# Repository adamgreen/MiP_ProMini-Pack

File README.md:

# MiP ProMini Pack - 16MHz/5V

# Archived - June 10th, 2021
This project is no longer under active development by me.<br>
@Tiogaplanet has his own fork which has been updated more recently than this version. It can be found at https://github.com/Tiogaplanet/MiP_Power_Up

# Attribution
This project is based on the now retired [Sparkfun MiP ProMini-Pack](https://www.sparkfun.com/products/retired/13058).<br>
The original Eagle files can be found on [GitHub](https://github.com/sparkfun/MiP_ProMini-Pack). They were created by
Sparkfun employee [Casey Kuhns](https://github.com/caseykuhns).

# Project Goals
* Produce a functional version of the MiP ProMini-Pack to correct the [MiP communication issue](https://github.com/WowWeeLabs/MiP-BLE-Protocol/issues/18) in the Sparkfun original.
* Run the ATMEGA328 at 16MHz instead of 8MHz. This allows the AVR to properly receive 115200 bps serial output from the
  MiP.
* Increase Vcc from 3.3V to 5V so that the ATMEGA328 can reliably run at 16MHz.
* Modify board layout to make it easier to hand solder the SMD parts.
  * Use larger 0805 passives instead of 0603.
  * Extend the pads on some of the SMD packages to allow for easier transfer of heat from the soldering iron.
* Port my [MiP C API](https://github.com/adamgreen/MiP-Capi) project to Arduino and refactor it to make it more closely resemble other Arduino libraries.
  * This library can be found within the [Arduino/MiP_ProMini_Pack_Library](Arduino/MiP_ProMini_Pack_Library#readme) folder of this GitHub repository.

# Links
* [MiP ProMini-Pack Arduino Library](Arduino/MiP_ProMini_Pack_Library#readme): The Arduino library for this MiP ProMini-Pack.<br>
* [WowWee's Official MiP Protocol Specification](https://github.com/WowWeeLabs/MiP-BLE-Protocol): Describes the serial protocol used by the Arduino library to communicate with the MiP.<br>
* [Sparkfun's MiP ProMini-Pack Installation Tutorial](https://learn.sparkfun.com/tutorials/hacking-the-mip---promini-pack): This retired Sparkfun tutorial is still the best place to learn about opening up your MiP and installing this MiP ProMini Pack.<br>
* [Tiogaplanet's MiP ProtoPack](https://github.com/Tiogaplanet/MiP_ProtoPack): A prototyping plug-in board to expand the MiP ProMini-Pack.<br>

# Bill of Materials
Description | Quantity | Part Number(s)
------------|----------|---------------
[TS3USB221A USB SWITCH DUAL - 10QFN](https://www.digikey.com/products/en?keywords=296-24019-1-ND) | 1 | U3
[ATMEGA328P - 32TQFP](https://www.digikey.com/products/en?keywords=ATMEGA328P-AURCT-ND) | 1 | U1
[16MHz Ceramic Resonator - 15pF ±0.2% SMD](https://www.digikey.com/products/en?keywords=490-1198-1-ND) | 1 | Q1
[MIC5205 Linear Regulator - 5.0V 150mA SOT23-5](https://www.digikey.com/products/en?keywords=576-1261-1-ND) | 1 | U2
[MIC5205 Linear Regulator - 3.3V 150mA SOT23-5](https://www.digikey.com/products/en?keywords=576-1259-1-ND) | 1 | U4
[10kΩ Resistor - 0805](https://www.adafruit.com/product/441) | 3 | R2, R4, R5
[1kΩ Resistor - 0805](https://www.adafruit.com/product/441) | 6 | R7, R8, R9, R10, R12, R13
[330Ω Resistor - 0805](https://www.adafruit.com/product/441) | 1 | R6
[0.1uF Capacitor - 0805](https://www.adafruit.com/product/441) | 6 | C1, C2, C3, C4, C5, C10
[10uF Capacitor - 1206](https://www.digikey.com/products/en?keywords=478-8235-1-ND) | 4 | C6, C7, C13, C19
[Diode Schottky 10V 570mA SOD323](https://www.digikey.com/products/en?keywords=ZLLS410CT-ND) | 1 | D1
[Green LED - 0603](https://www.digikey.com/products/en?keywords=160-1446-1-ND) | 2 | D3, D4
[PTC Resettable Fuse - 1206](https://www.digikey.com/products/en?keywords=507-1802-1-ND) | 1 | F1
[SPST Tactile SMD Switch - Normally Open](https://www.digikey.com/products/en?keywords=CKN9112CT-ND) | 1 | S1
[JST 4-position Connector - 1.5mm Through-Hole](https://www.digikey.com/products/en?keywords=455-1659-ND) | 1 | JP11
[Male Header for FTDI 1x6 - 0.1" Through-Hole](https://www.digikey.com/products/en?keywords=HDR100IMP40M-G-V-TH-ND) | 1 | JP1
[JST 4-wire Cable](https://www.digikey.com/product-detail/en/jst-sales-america-inc/A04ZR04ZR28H152A/455-3026-ND/6009402) | 1 |
[Screw - Phillips Head (1/2", 4-40)](https://www.sparkfun.com/products/10452) | 3 |
[Nut - (4-40)](https://www.sparkfun.com/products/10454) | 3 |
[Screw - Phillip Head (M3-0.5 x 12mm)](https://www.sparkfun.com/products/13227) | 3 |

# Schematic

# OSHPark Renderings of PCB

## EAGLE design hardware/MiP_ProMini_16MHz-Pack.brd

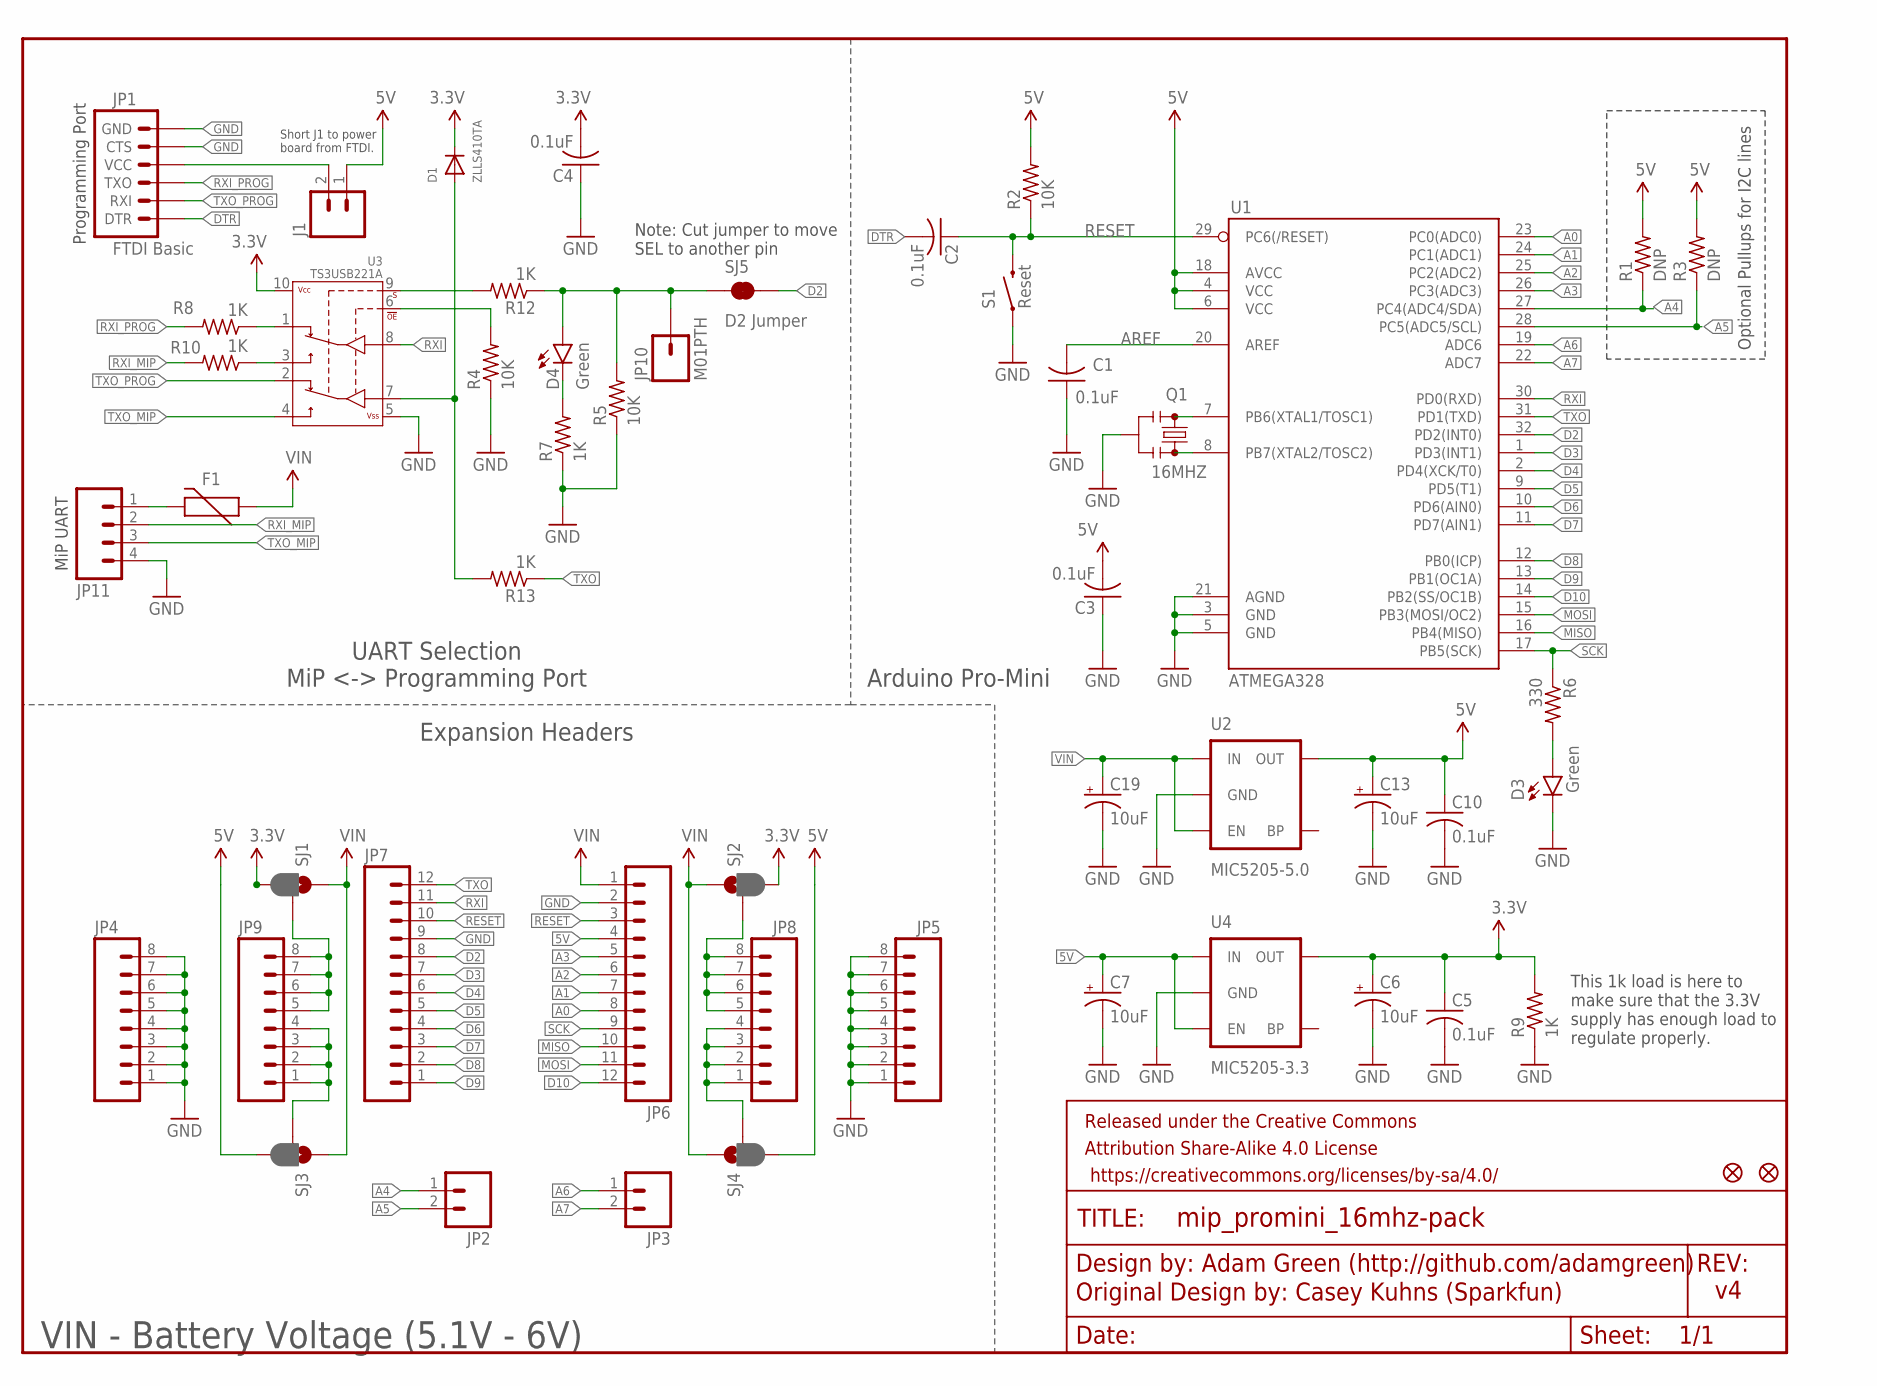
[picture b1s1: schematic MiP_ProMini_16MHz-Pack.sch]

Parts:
C1, C2, C3, C4, C5, C10: 0.1uF; C0805
C6, C7, C13, C19: 10uF; EIA3216
D1: ZLLS410TA; SOD-323F
D3, D4: Green; LED-0603
F1: PTCCUSTOM; PTC-1206-CUSTOM
FID1, FID2: FIDUCIAL1X2; FIDUCIAL-1X2
FRAME1: FRAME-LETTER; CREATIVE_COMMONS
J1: M02PTH; 1X02
JP1: FTDI Basic; 1X06
JP2, JP3: M02PTH; 1X02
JP4, JP5, JP8, JP9: M081X08; 1X08
JP6, JP7: M12PTH; 1X12
JP10: M01PTH; 1X01
JP11: M04JST; 1X04-1.5MM_JST
Q1: 16MHZ; RESONATOR-SMD-CUSTOM2
R1, R3: DNP; R0805
R2, R4, R5: 10K; R0805
R6: 330; R0805
R7, R8, R9, R10, R12, R13: 1K; R0805
S1: Reset; TACTILE-SWITCH-SMD-CKN9112CT-ND
SJ1, SJ2, SJ3, SJ4: JUMPER-PAD-3-2OF3_NC_BY_PASTE; PAD-JUMPER-3-2OF3_NC_BY_PASTE_YES_SILK_FULL_BOX
SJ5: D2 Jumper; PAD-JUMPER-2-NC_BY_TRACE_YES_SILK
U1: ATMEGA328; TQFP32-08
U2: MIC5205-5.0; SOT23-5
U3: TS3USB221A; QFN-10-RSE-CUSTOM
U4: MIC5205-3.3; SOT23-5

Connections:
3.3V: C4.2, C5.1, C6.A (+), D1.C, R9.2, SJ1.3, SJ2.3, U3.10 (VCC), U4.5 (OUT)
5V: C3.2, C7.A (+), C10.1, C13.A (+), J1.1, JP6.4, R1.2, R2.2, R3.2, SJ3.3, SJ4.3, U1.4 (VCC), U1.6 (VCC), U1.18 (AVCC), U2.5 (OUT), U4.1 (IN), U4.3 (EN)
A0: JP6.8, U1.23 (PC0(ADC0))
A1: JP6.7, U1.24 (PC1(ADC1))
A2: JP6.6, U1.25 (PC2(ADC2))
A3: JP6.5, U1.26 (PC3(ADC3))
A4: JP2.1, R1.1, U1.27 (PC4(ADC4/SDA))
A5: JP2.2, R3.1, U1.28 (PC5(ADC5/SCL))
A6: JP3.1, U1.19 (ADC6)
A7: JP3.2, U1.22 (ADC7)
AREF: C1.2, U1.20 (AREF)
D2: JP7.8, SJ5.2, U1.32 (PD2(INT0))
D3: JP7.7, U1.1 (PD3(INT1))
D4: JP7.6, U1.2 (PD4(XCK/T0))
D5: JP7.5, U1.9 (PD5(T1))
D6: JP7.4, U1.10 (PD6(AIN0))
D7: JP7.3, U1.11 (PD7(AIN1))
D8: JP7.2, U1.12 (PB0(ICP))
D9: JP7.1, U1.13 (PB1(OC1A))
D10: JP6.12, U1.14 (PB2(SS/OC1B))
DTR: C2.2, JP1.1 (DTR)
GND: C1.1, C3.1, C4.1, C5.2, C6.C (-), C7.C (-), C10.2, C13.C (-), C19.C (-), D3.C, JP1.5 (CTS), JP1.6 (GND), JP4.1, JP4.2, JP4.3, JP4.4, JP4.5, JP4.6, JP4.7, JP4.8, JP5.1, JP5.2, JP5.3, JP5.4, JP5.5, JP5.6, JP5.7, JP5.8, JP6.2, JP7.9, JP11.4, Q1.2, R4.1, R5.1, R7.1, R9.1, S1.1, U1.3 (GND), U1.5 (GND), U1.21 (AGND), U2.2 (GND), U3.5 (VSS), U4.2 (GND)
MISO: JP6.10, U1.16 (PB4(MISO))
MOSI: JP6.11, U1.15 (PB3(MOSI/OC2))
unnamed: Q1.3, U1.8 (PB7(XTAL2/TOSC2))
unnamed: JP9.5, JP9.6, JP9.7, JP9.8, SJ1.2
unnamed: JP9.1, JP9.2, JP9.3, JP9.4, SJ3.2
unnamed: Q1.1, U1.7 (PB6(XTAL1/TOSC1))
unnamed: JP8.5, JP8.6, JP8.7, JP8.8, SJ2.2
unnamed: JP8.1, JP8.2, JP8.3, JP8.4, SJ4.2
unnamed: D3.A, R6.2
unnamed: D4.C, R7.2
unnamed: R10.1, U3.3 (2D+)
unnamed: R8.1, U3.1 (1D+)
unnamed: R4.2, U3.6 (!OE)
unnamed: J1.2, JP1.4 (VCC)
unnamed: R12.2, U3.9 (S)
unnamed: F1.2, JP11.1
unnamed: D1.A, R13.2, U3.7 (D-)
RESET: C2.1, JP6.3, JP7.10, R2.1, S1.3 (2), U1.29 (PC6(/RESET))
RXI: JP7.11, U1.30 (PD0(RXD)), U3.8 (D+)
RXI_MIP: JP11.2, R10.2
RXI_PROG: JP1.3 (TXO), R8.2
SCK: JP6.9, R6.1, U1.17 (PB5(SCK))
SELECT: D4.A, JP10.1, R5.2, R12.1, SJ5.1
TXO: JP7.12, R13.1, U1.31 (PD1(TXD))
TXO_MIP: JP11.3, U3.4 (2D-)
TXO_PROG: JP1.2 (RXI), U3.2 (1D-)
VIN: C19.A (+), F1.1, JP6.1, SJ1.1, SJ2.1, SJ3.1, SJ4.1, U2.1 (IN), U2.3 (EN)

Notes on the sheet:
Optional Pullups for I2C lines
Adam Green (http://github.com/adamgreen)
Note: Cut jumper to move SEL to another pin
MiP UART
Programming Port
UART Selection MiP <-> Programming Port
Expansion Headers
Arduino Pro-Mini
VIN - Battery Voltage (5.1V - 6V)
Original Design by: Casey Kuhns (Sparkfun)
Short J1 to power board from FTDI.
This 1k load is here to make sure that the 3.3V supply has enough load to regulate properly.

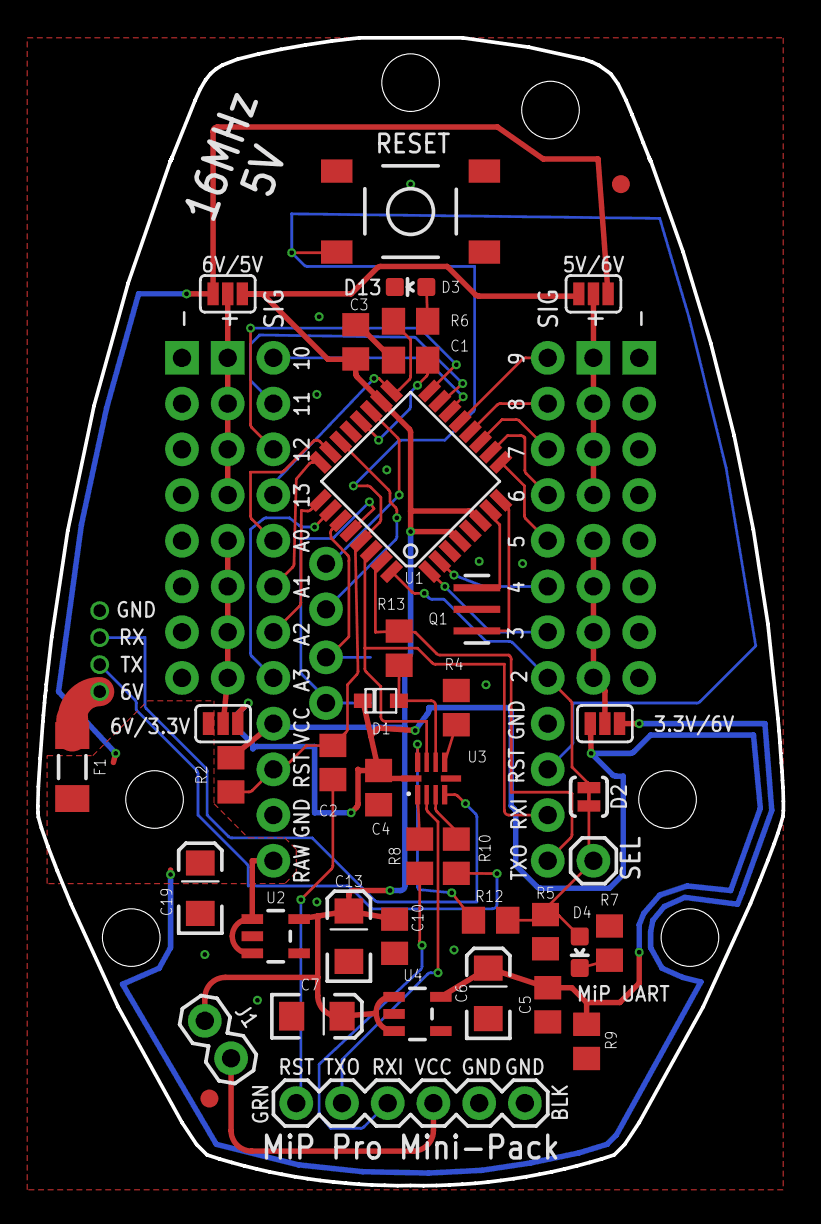
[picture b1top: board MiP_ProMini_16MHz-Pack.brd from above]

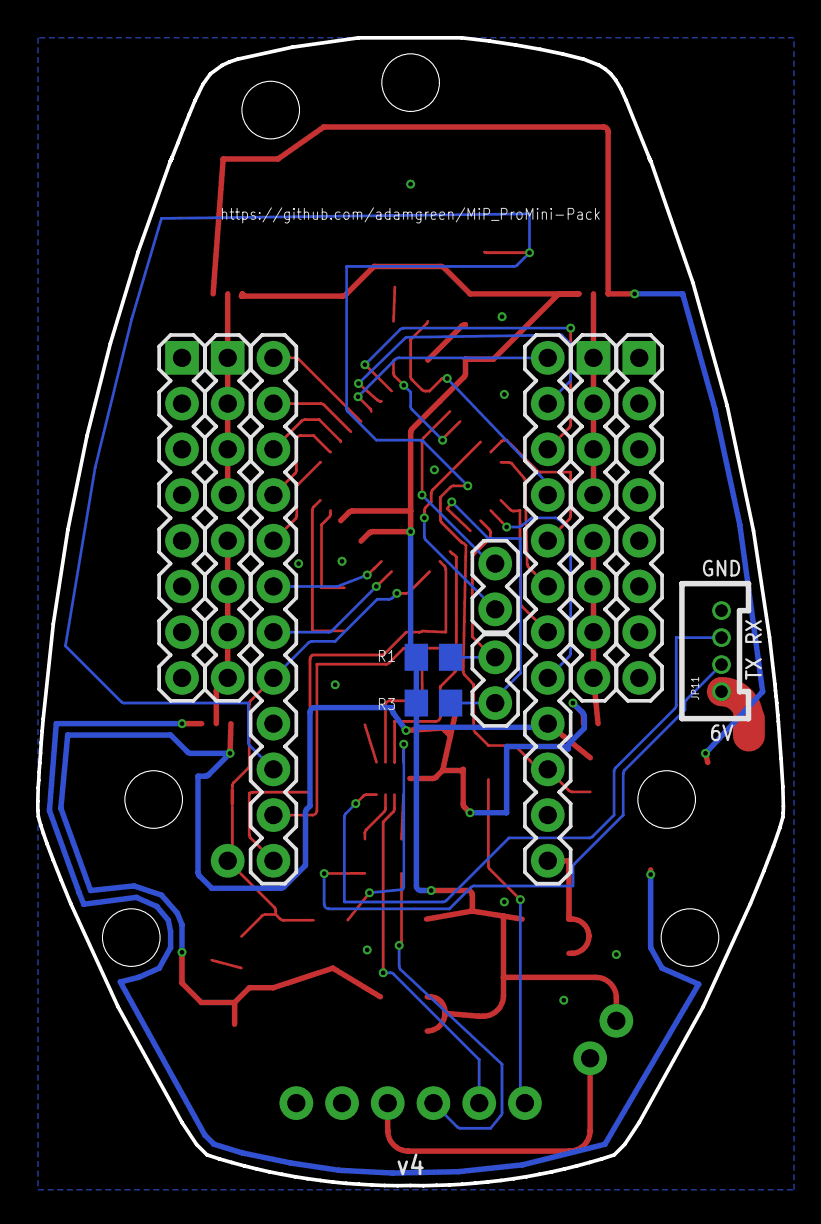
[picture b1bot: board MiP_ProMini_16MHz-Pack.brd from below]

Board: 2 copper layers, 41.4 x 63.8 mm, 52 parts (11 on the bottom side), 49 nets.

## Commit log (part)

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2017-10-14 Add overview to README
2018-02-26 Rename Eagle files
    Remove Sparkfun from filenames since I don't want to infringe on their
    trademark for my variation of the board.
2018-02-26 Update schematic to 16MHz / 5V
    The ATMEGA328 can't reliably receive data from the MiP at 115200 bps
    when running at 8MHz. This commit bumps the clock rate up to 16MHz and
    bumps the voltage up to 5V so that the AVR can reliably run at this
    higher rate.
    Other changes to the schematic include:
    * By default the VCC pin of the FTDI header is no longer connected to
2018-03-07 Adding CC license text to hardware folder
2018-03-10 Initial layout complete
    No more air wires to route and passes OSHPark DRC.
    Important notes:
    * I had to move the A6/A7 1x2 jumper block to move the AVR up higher on
    the board. This was done to make more room for larger passives and an
    extra voltage regulator lower on the board.
    * I ended up removing the AVR-ISP port since I couldn't fit it on the
2018-03-10 Update README
    Added notes about what was changed on PCB to make soldering easier and
    removed the AVRISP header item since it wasn't convenient to place and
    route.
2018-03-10 Tidy up silkscreen names
    I moved some of the part names around so that they would be a bit
    easier to read (small size will still make them tricky to read). I also
    smashed some parts and removed names/values all together since they
    just made things more cluttered and confusing.
2018-03-10 Adding PCB images from OSHPark
    These are OSHPark generated images of the top/bottom sides of the PCB
    that I sent off to have made today.
2018-03-10 Add schematic image
2018-03-10 Version 3 - Route all power headers on top layer
    Previously I had the upper right power rail in the user prototype area
    routed on the bottom layer whereas the rest were routed on the bottom.
    This commit makes them all the same and makes it easier for the user
    to see which pads are connected to what just by looking at the traces
    through the top soldermask.
2018-03-10 Update schematic version to 3
    I should have done this earlier when I removed the AVR-ISP header,
    etc.
2018-03-11 Added tRestrict to 16MHz resonator part
    This keeps the ground plane and wires out of the tStop area that was
    already defined for the resonator.
2018-04-16 Add photos of new PCB
2018-04-16 Move images to their own folder
2018-04-16 Update README.md
    Add photo of PCB mounted on back of MiP.
2018-04-19 Convert C API to C++
2018-04-19 Update PRINT & PRINTLN macros
    No longer hardcodes the UART select pin and instead uses static methods
    on the MiP class to switch the UART between the MiP and PC.
2018-04-20 Pull transport layer into MiP class
    This gets rid of mip-arduino.cpp and mip-transport.h as all the
    required code from these sources has been pulled into mip.h and mip.cpp
    Other updates include:
    * Default releaseSerialToPc in the constructor to false. This allows
    MiP out of band notifications to be captured more reliably but does
    mean that users of the MiP object must switch Serial back to the PC
2018-04-20 Don't return early on found response
    Continue to process any other bytes in the recieve buffer even when
    the expected response for the last request has been encountered. This
    would allow something like a getStatus() call to receive the actual
    data returned for its request and not an older OOB perioidic status
    notification.
2018-04-20 Handle MIP_REQUEST_DELAY differently
    Previously transportSendRequest() would just call delay() for this
    number of milliseconds to make sure that no two requests could be
    issued in less time than this. Now it just delays at the top of the
    function if this many milliseconds haven't already elapsed since it
    was last called. This lets the caller use the CPU to do something
    else between calls if they want.
2018-04-20 API cleanup
    API updates include:
    * Switch most of the structs to classes with constructors.
    * Use references for passing output objects into APIs instead of
    pointers.
    * Notification related functions will now fail with a
    MIP_NO_NOTIFICATIONS error if releaseSerialToPC isn't set to false in
2018-04-22 Fix compiler warnings
    I bumped the warning level up to "All" in the Arduino IDE and fixed
    the resulting warnings.
    Changes include:
    * Adding a MIP_PRINT_ERRORS() macro to mip.h which checks a result code
    returned from a MiP method and prints out an error message if the
    result isn't MIP_ERROR_NONE. Actually reading the result code this
2018-04-24 Make the library API more Arduino friendly
    This commit is mostly about simplifying the API model and bringing it
    closer to other Arduino APIs.
    The changes in this commit include:
    * When mip.h is included in a user's program, it now substitutes all of
    their usage of Serial with MiPStream. For example,
    "Serial.println("Sample")" will actually become
2018-04-26 Adding Arduino API documentation
    This is my first attempt at documenting the library I created for
    Arduino.
2018-04-26 Ignore redundant begin/end calls on MiPStream
    This commit also hardcodes the Serial rate to 115200 as required by the
    MiP.
2018-04-26 Update API documentation
    Changes include:
    * When using the serial port, I don't seem to need the 0.5 seconds
    between distanceDrive commands. I have updated the example code and
    the documentation to remove references to this delay.
    * Add notes indicating that the MiP sends status update notifications
    roughly every 30 seconds.
2018-04-26 Can now call playSoundList multiple times
    Previously you could only call playSoundList() once and then you had to
    use beginSoundList() and addEntryToSoundList() to rebuild the list
    before playing again. Now you can play the same list over and over
    again if you need.
2018-04-27 Add a 1k load across 3.3V supply
    Without this load, the 3.3V supply was closer to 4.4V. The datasheet
    for the regulator indicates that it doesn't have a minimum load to
    maintain regulation but it also indicates that the output capacitance
    can be closer to 0.5uF when the output current is only 1mA. If a
    person was using the 3.3V supply for something else that was putting
    a >= 1mA load on it then they could omit this resistor. Lowering the
2018-04-27 Update content for version 3
    * I moved the name marking for R9 so that it wasn't so cramped.
    * I uploaded the OSH Park PCB renderings of version 3.
    * I uploaded the latest schematic as well.
2018-04-27 Update main README
    * Switch to renderings of version 3 for the schematics and PCBs.
    * Highlight the fact that a new Arduino library was written as well
2018-05-23 Reordered BOM list
    The reordered the list to match the order that I solder them.
2018-07-01 DisconnectApp
    Added the disconnectApp function to disconnect all apps connected to the
    MiP.
2018-07-02 Fix issue #3 - Refactor sound playing API
    * Added playSound() function which makes it much easier for a user to
    start the MiP immediately playing a single sound. No need to use the
    sound list to queue up sounds and then signal the MiP to start
    playing the queue.
    * Updated addEntryToSoundList() to accept an optional volume parameter.
    This makes it easier for the user to set the volume to be used for
2018-07-03 Latest work to implement different game modes.
    Latest work, setters are working, readGameMode needs debugging.
2018-07-03 Added example EnableGameMode.ino
    Tests the new enable mode functionality.
2018-07-03 Edits based on feedback
    Incorporated all inputs from @adamgreen and added an example sketch.
2018-07-03 trim trailing space
2018-07-03 Documentation update.
    Updated the readme with documentation for the new game modes functions.
2018-07-04 Stop before issuing actual set/get game mode commands
    I updated rawSetGameMode() and rawGetGameMode() to call stop() before
    running the actual set/get game mode command. This allows the MiP to
    accept those commands more reliably when it is actively moving around
    as part of the current game mode.
    The rawGetGameMode() command will reinstate the previously stopped game
    mode once the mode has been successfully received from the MiP.
2018-07-04 Updated the MiP library readme file.
    Added more descriptive language for the enable mode functions.
2018-07-04 Trying to get read/write EEPROM working
    Wrote setUserData() and gerUserData().
2018-07-04 Incremental improvement to reading/writing EEPROM
    I found a couple obvious bugs in creating the mip command array to send
    to the mip. Added some documentaton. Will link example in readme
    later.
2018-07-09 Remove trailing whitespace from examples
    @Tiagoplanet removed most of these (left by my editor) and I am just
    cleaning up the rest.
2018-07-09 Cleanup examples
    I made changes to the examples to make them more like other Arduino
    samples I see out in the wild. These changes include:
    * Running Cmd+T to run the auto format tool. This changes the
    indentation to 2 spaces per level instead of the 4 I tend to use
    in my code. The only indentation descrepancy I maintained was to
    indent print()/println() that output to the same line as the
2018-07-09 Remove extra space from DistanceDrive
2018-07-10 Switch return of None to Nothing
    @Tiagoplanet cleaned up most of the inconsistencies I had in the
    documentation and I am just cleaning up a few more with this commit.
2018-07-15 Trying to get IR working
    Trying to implement send/receive IR dongle code.
2018-07-20 Add Detection mode and refine last commit
    Enabling the other IR functions like detection mode in attempt to get
    two MiPs talking via IR.
2018-07-22 closing in on receive IR dongle code
    A little more representative of what I'm trying to accomplish.
2018-07-25 Commit for code review
2018-07-25 Another review commit
    I was dumping the buffer twice, line breaks in the wrong places, amateur
    hour over here.
2018-08-01 Preparing for IR PR again.
    This represents my submission for inclusion of IR support in the
    library.
2018-08-10 Add 4-wire JST connector to BOM
    This is the cable used to connect MiP UART/Power to the MiP ProMini board.
2018-09-02 README updates
    * Add links section.
    * Added a note that the most important goal of this project is to fix
    the serial communication issue in the Sparkfun original.
    * Reordered some BOM items to match the order that I now solder them.
2018-09-03 Update README.md
    Fix indentation of recently added goal.
2018-09-03 Add Tiogaplanet's MiP ProtoPack link to README
    Manually applies change from PR #12
2018-09-04 Add hardware to BOM
    Added links to required hardware from Sparkfun's website.
2018-09-05 Auto switch to 9600 baud for newer MiP robots
    The MiP::begin() call will now attempt to first connect at 115200 baud
    and then fallback to 9600 baud if that fails. This allows the library
    to work with both new and older MiP robots...it just takes a bit longer
    to connect with the newer MiP robots while it tries 115200 baud first.
2018-09-22 Interleave 115200 and 9600 baud init attempts
    Fixes issue #14.
    Fix is based on @Tiogaplanet 's feedback to my previous commit.
2018-10-09 Add unverified LED update APIs
    Implements feature request #15. These new APIs allow the chest LED and
    head LEDs to be set without the overhead of verifying that the MiP
    successfully received and applied the LED state change. Can be useful
    if the developer will be setting the LED state multiple times per
    second anyway so that a missed state change wouldn't be noticed by a
    user.

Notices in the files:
parts and their libraries:
SparkFun-Aesthetics: Licensing: Creative Commons ShareAlike 4.0 International - https://creativecommons.org/licenses/by-sa/4.0
SparkFun-Aesthetics: Released under the Creative Commons Attribution Share-Alike 4.0 License
SparkFun-Aesthetics: https://creativecommons.org/licenses/by-sa/4.0
